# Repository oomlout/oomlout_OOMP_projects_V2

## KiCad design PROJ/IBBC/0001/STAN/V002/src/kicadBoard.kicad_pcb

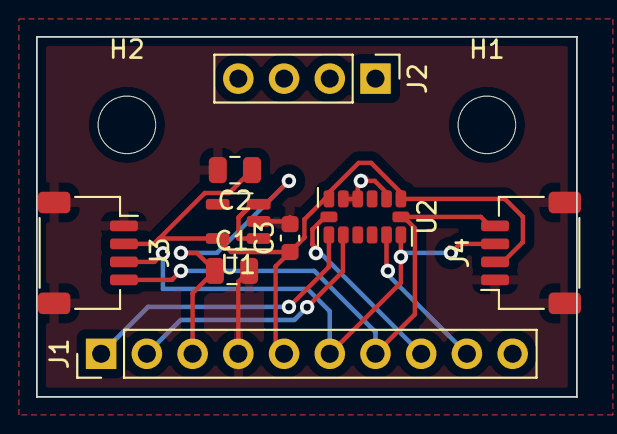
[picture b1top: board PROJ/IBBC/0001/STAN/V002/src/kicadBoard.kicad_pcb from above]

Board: 2 copper layers, 30.0 x 20.0 mm, 11 parts (0 on the bottom side), 9 nets.

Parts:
C1, C2: 10uf; C_0805_2012Metric
C3: 100nf; C_0603_1608Metric
H1, H2: MountingHole; MountingHole_3.2mm_M3
J1: HEAD-I01-X-PI10-01 oom.lt/H10; PinHeader_1x10_P2.54mm_Vertical
J2: HEAD-I01-X-PI04-01 oom.lt/H4; PinHeader_1x04_P2.54mm_Vertical
J3, J4: HEAD-JSTSH-X-PI04-RS oom.lt/HSHR4; JST_SH_SM04B-SRSS-TB_1x04-1MP_P1.00mm_Horizontal
U1: AP2112K-3.3; SOT-23-5
U2: ADXL343; LGA-14_3x5mm_P0.8mm_LayoutBorder1x6y

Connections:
3v3: C2.1, C3.1, J1.5, J3.2, J4.2, U1.5 (VOUT), U2.1 (Vdd_I/O), U2.6 (Vs)
CS: J1.8, U2.7 (~CS)
EX01: J1.1, U2.8 (INT1)
EX02: J1.2, U2.9 (INT2)
EX03: J1.9, U2.12 (SDO/ADDR)
GND: C1.2, C2.2, C3.2, J1.4, J3.1, J3.MP (MountPin), J4.1, J4.MP (MountPin), U1.2 (GND), U2.2 (GND), U2.4 (GND), U2.5 (GND)
SCL: J1.7, J3.4, J4.4, U2.14 (SCL/SCLK)
SDA: J1.6, J3.3, J4.3, U2.13 (SDA/SDI/SDIO)
Vin: C1.1, J1.3, U1.1 (VIN), U1.3 (EN)

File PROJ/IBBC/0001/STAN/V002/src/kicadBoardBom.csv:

"Id";"Designator";"Package";"Quantity";"Designation";"Supplier and ref";
1;"C2,C1";"C_0805_2012Metric";2;"10uf";;;
2;"J1";"PinHeader_1x10_P2.54mm_Vertical";1;"HEAD-I01-X-PI10-01 oom.lt/H10";;;
3;"U1";"SOT-23-5";1;"AP2112K-3.3";;;
4;"J4,J3";"JST_SH_SM04B-SRSS-TB_1x04-1MP_P1.00mm_Horizontal";2;"HEAD-JSTSH-X-PI04-RS oom.lt/HSHR4";;;
5;"U2";"LGA-14_3x5mm_P0.8mm_LayoutBorder1x6y";1;"ADXL343";;;
6;"J2";"PinHeader_1x04_P2.54mm_Vertical";1;"HEAD-I01-X-PI04-01 oom.lt/H4";;;
7;"H2,H1";"MountingHole_3.2mm_M3";2;"MountingHole";;;
8;"C3";"C_0603_1608Metric";1;"100nf";;;

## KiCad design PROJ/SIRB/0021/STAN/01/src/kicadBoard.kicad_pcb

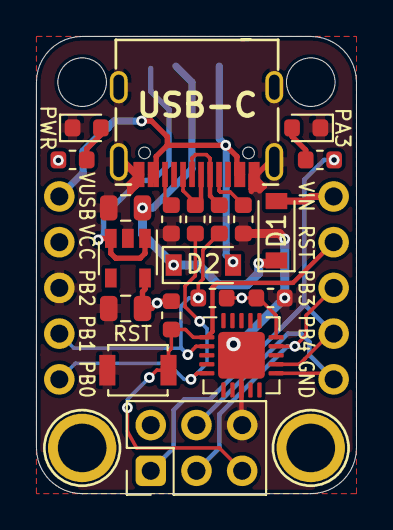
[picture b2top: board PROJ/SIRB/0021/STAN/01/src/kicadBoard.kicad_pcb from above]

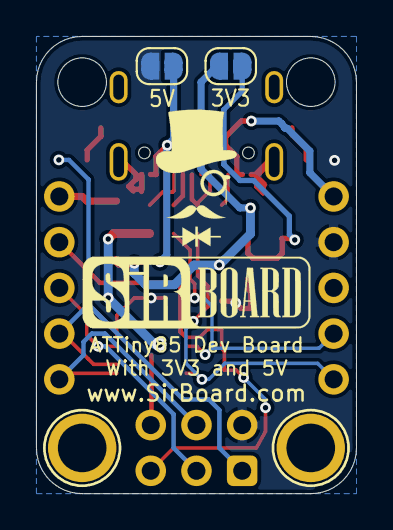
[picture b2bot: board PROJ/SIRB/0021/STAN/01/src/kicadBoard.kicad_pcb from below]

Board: 2 copper layers, 17.8 x 25.4 mm, 28 parts (4 on the bottom side), 18 nets.

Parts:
3V3, 5V: SolderJumper_2_Open; SolderJumper-2_P1.3mm_Open_RoundedPad1.0x1.5mm
C1, C2: 10uF; C_0805_2012Metric
C3: 100nF; C_0603_1608Metric
D1, D2: MBR120; D_SOD-123
H1, H4: MountingHole; MountingHole_2.7mm_M2.5
H2, H3: MountingHole; MountingHole_M2.5_SirBoard
J2, J3: Conn_01x05; PinHeader_1x05_P2.54mm_Vertical
J4: ISP6; PinHeader_2x03_P2.54mm_Vertical
PA3: RED; LED_0603_1608Metric
PWR: RED; LED_0603_1608Metric
R1, R2: 5k1; R_0603_1608Metric
R3, R4: 68e; R_0603_1608Metric
R5: 10K; R_0603_1608Metric
R6: 1k5; R_0603_1608Metric
R7, R8: 1K; R_0603_1608Metric
RST: SW_SPST; SW_SPST_B3U-1000P
U1: ATtiny85-20MU; QFN-20-1EP_4x4mm_P0.5mm_EP2.6x2.6mm
U2: SPX3819M5-L-3-3; SOT-23-5
USB-C: USB_C_Receptacle_USB2.0; USB_C

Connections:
GND: C1.2, C2.2, C3.2, J2.3, J4.6, PA3.1, PWR.1, R1.2, R2.2, RST.2, U1.8, U1.21, U2.2, USB-C.A1, USB-C.A12, USB-C.B1, USB-C.B12, USB-C.S1
unnamed: 3V3.1, C1.1, D1.1, D2.1
unnamed: 3V3.2, U2.1, U2.3
unnamed: PA3.2, R7.1
unnamed: PWR.2, R8.1
unnamed: R2.1, USB-C.A5
unnamed: R4.1, USB-C.A6, USB-C.B6
unnamed: R3.1, USB-C.A7, USB-C.B7
unnamed: R1.1, USB-C.B5
PB0: J3.5, J4.4, U1.11
PB1: J3.4, J4.1, R7.2, U1.12
PB2: J3.3, J4.3, U1.14
PB3: J2.4, R3.2, R6.1, U1.2
PB4: J2.5, R4.2, U1.5
RST: J3.2, J4.5, R5.1, RST.1, U1.1
VCC: 5V.2, C2.1, C3.1, J2.2, J4.2, R5.2, R6.2, R8.2, U1.15, U2.5
VIN: D1.2, J3.1
VUSB: 5V.1, D2.2, J2.1, USB-C.A4, USB-C.A9, USB-C.B4, USB-C.B9

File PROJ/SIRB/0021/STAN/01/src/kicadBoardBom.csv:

"Id";"Designator";"Package";"Quantity";"Designation";"Supplier and ref";
1;"G***";"SirBoard127x40";1;"LOGO";;;
2;"G***";"logo76x107";1;"LOGO";;;
3;"C3";"C_0603_1608Metric";1;"100nF";;;
4;"U1";"QFN-20-1EP_4x4mm_P0.5mm_EP2.6x2.6mm";1;"ATtiny85-20MU";;;
5;"J2,J3";"PinHeader_1x05_P2.54mm_Vertical";2;"Conn_01x05";;;
6;"U2";"SOT-23-5";1;"SPX3819M5-L-3-3";;;
7;"RST";"SW_SPST_B3U-1000P";1;"SW_SPST";;;
8;"R8,R7";"R_0603_1608Metric";2;"1K";;;
9;"R6";"R_0603_1608Metric";1;"1k5";;;
10;"R5";"R_0603_1608Metric";1;"10K";;;
11;"R4,R3";"R_0603_1608Metric";2;"68e";;;
12;"R2,R1";"R_0603_1608Metric";2;"5k1";;;
13;"J4";"PinHeader_2x03_P2.54mm_Vertical";1;"ISP6";;;
14;"USB-C";"USB_C";1;"USB_C_Receptacle_USB2.0";;;
15;"PWR,PA3";"LED_0603_1608Metric";2;"RED";;;
16;"D2,D1";"D_SOD-123";2;"MBR120";;;
17;"C2,C1";"C_0805_2012Metric";2;"10uF";;;

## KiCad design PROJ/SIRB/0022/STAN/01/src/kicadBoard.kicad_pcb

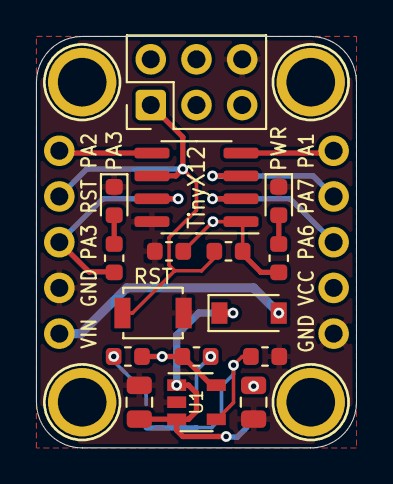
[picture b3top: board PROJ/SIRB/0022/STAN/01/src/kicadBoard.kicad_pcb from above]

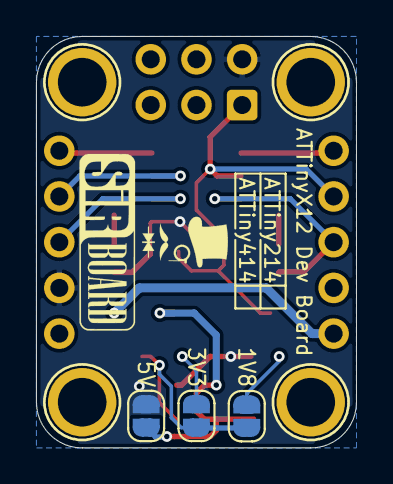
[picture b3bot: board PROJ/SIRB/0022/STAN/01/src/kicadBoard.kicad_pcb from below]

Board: 2 copper layers, 17.8 x 22.9 mm, 25 parts (5 on the bottom side), 15 nets.

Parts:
1V8, 3V3: SolderJumper_2_Open; SolderJumper-2_P1.3mm_Open_RoundedPad1.0x1.5mm
5V: SolderJumper_2_Bridged; SolderJumper-2_P1.3mm_Open_RoundedPad1.0x1.5mm
C1: 10uF; C_0805_2012Metric
C2: 2u2; C_0805_2012Metric
C3: 100nF; C_0603_1608Metric
D1: MBR120; D_SOD-123
H1, H2, H3, H4: MountingHole; MountingHole_M2.5_SirBoard
J1, J2: Conn_01x05; PinHeader_1x05_P2.54mm_Vertical
J4: UPDI; PinHeader_2x03_P2.54mm_Vertical
PA3: BLUE; LED_0603_1608Metric
PWR: RED; LED_0603_1608Metric
R1, R7: 1k; R_0603_1608Metric
R3: 39k; R_0603_1608Metric
R4: 12.4k; R_0603_1608Metric
R5: 18k; R_0603_1608Metric
R6: 10k; R_0603_1608Metric
RST: RST; SW_SPST_B3U-1000P
TinyX12: ATtiny412; SOIC-8_3.9x4.9mm_P1.27mm
U1: AP7365; SOT-23-5

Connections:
/1V8: 1V8.2, R5.2
/3V3: 3V3.2, R3.2
/ADJ: 1V8.1, 3V3.1, R4.1, U1.4
GND: C1.2, C2.2, C3.2, J1.1, J2.2, J4.6, PA3.1, PWR.1, R4.2, RST.2, TinyX12.8, U1.2
unnamed: 5V.1, C1.1, D1.1, U1.1, U1.3
unnamed: PWR.2, R1.2
unnamed: PA3.2, R7.2
PA1: J1.5, TinyX12.4
PA2: J2.5, TinyX12.5
PA3: J2.3, R7.1, TinyX12.7
PA6: J1.3, TinyX12.2
PA7: J1.4, TinyX12.3
RST: J2.4, J4.1, R6.2, RST.1, TinyX12.6
VCC: 5V.2, C2.1, C3.1, J1.2, J4.2, R1.1, R3.1, R5.1, R6.1, TinyX12.1, U1.5
VIN: D1.2, J2.1

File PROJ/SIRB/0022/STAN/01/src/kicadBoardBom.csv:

"Id";"Designator";"Package";"Quantity";"Designation";"Supplier and ref";
1;"G***";"logo47x67";1;"LOGO";;;
2;"D1";"D_SOD-123";1;"MBR120";;;
3;"G***";"SirBoard98x31";1;"LOGO";;;
4;"C3";"C_0603_1608Metric";1;"100nF";;;
5;"C1";"C_0805_2012Metric";1;"10uF";;;
6;"C2";"C_0805_2012Metric";1;"2u2";;;
7;"J2,J1";"PinHeader_1x05_P2.54mm_Vertical";2;"Conn_01x05";;;
8;"TinyX12";"SOIC-8_3.9x4.9mm_P1.27mm";1;"ATtiny412";;;
9;"U1";"SOT-23-5";1;"AP7365";;;
10;"RST";"SW_SPST_B3U-1000P";1;"RST";;;
11;"R7,R1";"R_0603_1608Metric";2;"1k";;;
12;"R6";"R_0603_1608Metric";1;"10k";;;
13;"R5";"R_0603_1608Metric";1;"18k";;;
14;"R4";"R_0603_1608Metric";1;"12.4k";;;
15;"R3";"R_0603_1608Metric";1;"39k";;;
16;"J4";"PinHeader_2x03_P2.54mm_Vertical";1;"UPDI";;;
17;"PA3";"LED_0603_1608Metric";1;"BLUE";;;
18;"PWR";"LED_0603_1608Metric";1;"RED";;;

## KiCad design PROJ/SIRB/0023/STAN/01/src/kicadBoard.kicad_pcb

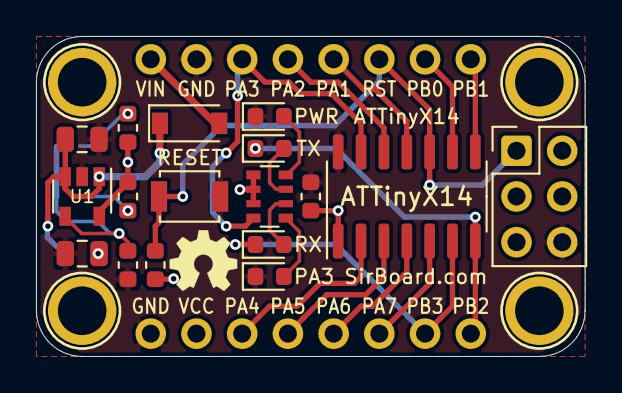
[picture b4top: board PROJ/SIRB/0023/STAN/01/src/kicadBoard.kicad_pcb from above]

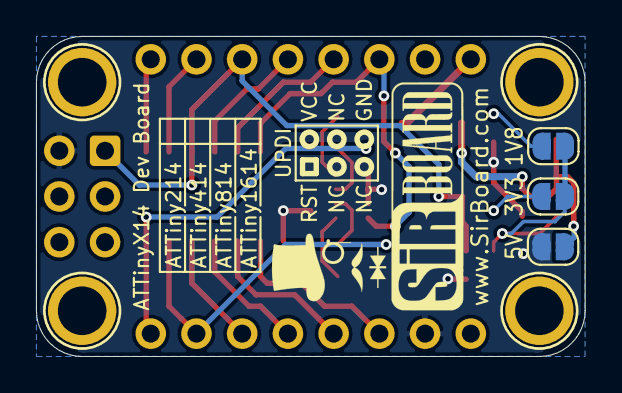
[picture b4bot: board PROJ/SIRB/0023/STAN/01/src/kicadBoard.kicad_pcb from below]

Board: 2 copper layers, 30.5 x 17.8 mm, 26 parts (5 on the bottom side), 23 nets.

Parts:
1V8, 3V3, 5V: SolderJumper_2_Open; SolderJumper-2_P1.3mm_Open_RoundedPad1.0x1.5mm
ATTinyX14: ATtiny1614-SS; SOIC-14_3.9x8.7mm_P1.27mm
C1: 10uF; C_0805_2012Metric
C2: 2u2; C_0805_2012Metric
C3: 100nF; C_0603_1608Metric
D1: MBR120; D_SOD-123
H1, H2, H3, H4: MountingHole; MountingHole_M2.5_SirBoard
J1, J2: Conn_01x08; PinHeader_1x08_P2.54mm_Vertical
J4: UPDI; PinHeader_2x03_P2.54mm_Vertical
PA3: BLUE; LED_0603_1608Metric
PWR: RED; LED_0603_1608Metric
R3: 39k; R_0603_1608Metric
R4: 12.4k; R_0603_1608Metric
R5: 18k; R_0603_1608Metric
R6: 10k; R_0603_1608Metric
RESET: RST; SW_SPST_B3U-1000P
RN1: 330E; R_Array_Convex_4x0603
RX: YEL; LED_0603_1608Metric
TX: YEL; LED_0603_1608Metric
U1: AP7365; SOT-23-5

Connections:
/1V8: 1V8.2, R5.2
/3V3: 3V3.2, R3.2
/ADJ: 1V8.1, 3V3.1, R4.1, U1.4
GND: ATTinyX14.14, C1.2, C2.2, C3.2, J1.1, J2.2, J4.6, PA3.1, PWR.1, R4.2, RESET.2, U1.2
unnamed: 5V.2, C1.1, D1.1, U1.1, U1.3
unnamed: PA3.2, RN1.1
unnamed: PWR.2, RN1.4
unnamed: RN1.2, RX.2
unnamed: RN1.3, TX.2
PA1: ATTinyX14.11, J2.5
PA2: ATTinyX14.12, J2.4
PA3: ATTinyX14.13, J2.3, RN1.8
PA4: ATTinyX14.2, J1.3
PA5: ATTinyX14.3, J1.4
PA6: ATTinyX14.4, J1.5
PA7: ATTinyX14.5, J1.6
PB0: ATTinyX14.9, J2.7
PB1: ATTinyX14.8, J2.8
RST: ATTinyX14.10, J2.6, J4.1, R6.2, RESET.1
RXD: ATTinyX14.6, J1.7, RX.1
TXD: ATTinyX14.7, J1.8, TX.1
VCC: 5V.1, ATTinyX14.1, C2.1, C3.1, J1.2, J4.2, R3.1, R5.1, R6.1, RN1.5, RN1.6, RN1.7, U1.5
VIN: D1.2, J2.1

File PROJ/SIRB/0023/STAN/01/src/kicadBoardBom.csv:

"Id";"Designator";"Package";"Quantity";"Designation";"Supplier and ref";
1;"G***";"SirBoard127x40";1;"LOGO";;;
2;"G***";"logo63x89";1;"LOGO";;;
3;"G***";"OSHW55x39";1;"LOGO";;;
4;"RN1";"R_Array_Convex_4x0603";1;"330E";;;
5;"TX,RX";"LED_0603_1608Metric";2;"YEL";;;
6;"ATTinyX14";"SOIC-14_3.9x8.7mm_P1.27mm";1;"ATtiny1614-SS";;;
7;"J2,J1";"PinHeader_1x08_P2.54mm_Vertical";2;"Conn_01x08";;;
8;"D1";"D_SOD-123";1;"MBR120";;;
9;"C3";"C_0603_1608Metric";1;"100nF";;;
10;"C1";"C_0805_2012Metric";1;"10uF";;;
11;"C2";"C_0805_2012Metric";1;"2u2";;;
12;"U1";"SOT-23-5";1;"AP7365";;;
13;"RESET";"SW_SPST_B3U-1000P";1;"RST";;;
14;"R6";"R_0603_1608Metric";1;"10k";;;
15;"R5";"R_0603_1608Metric";1;"18k";;;
16;"R4";"R_0603_1608Metric";1;"12.4k";;;
17;"R3";"R_0603_1608Metric";1;"39k";;;
18;"J4";"PinHeader_2x03_P2.54mm_Vertical";1;"UPDI";;;
19;"PA3";"LED_0603_1608Metric";1;"BLUE";;;
20;"PWR";"LED_0603_1608Metric";1;"RED";;;

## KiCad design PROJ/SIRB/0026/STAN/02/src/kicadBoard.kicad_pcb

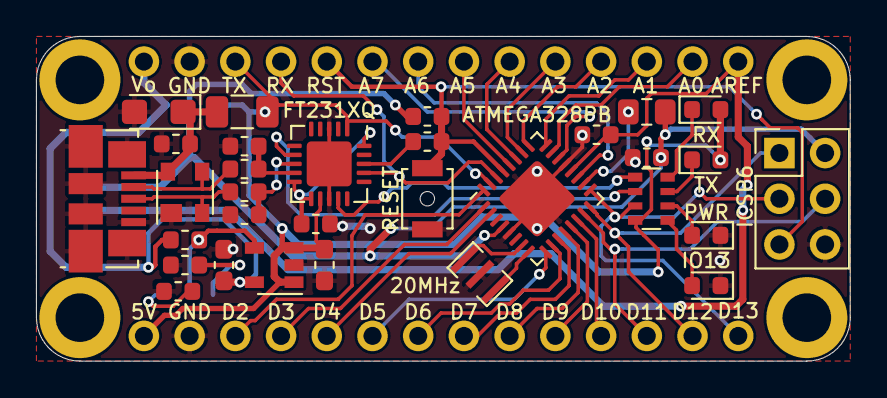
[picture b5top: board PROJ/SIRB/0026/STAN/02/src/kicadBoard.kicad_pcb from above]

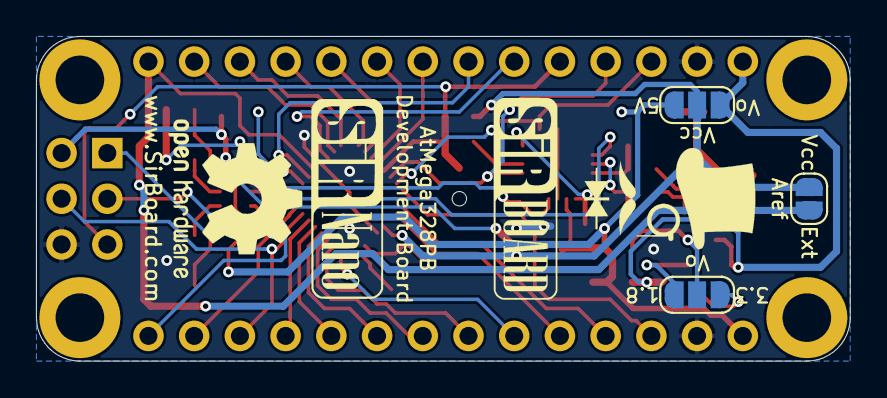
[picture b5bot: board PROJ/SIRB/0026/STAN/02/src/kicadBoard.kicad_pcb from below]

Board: 2 copper layers, 45.2 x 18.0 mm, 36 parts (5 on the bottom side), 47 nets.

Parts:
20MHz: 20MHz; Resonator_SMD_muRata_CSTxExxV-3Pin_3.0x1.1mm
C1, C3, C11: 100nF; C_0603_1608Metric
C2, C4: 47pF; C_0603_1608Metric
C6: 10nF; C_0603_1608Metric
C7: 1uF; C_0603_1608Metric
C8: 22uF; CP_EIA-3216-12_Kemet-S
C9, C10: 1uF; C_0603_1608Metric_Pad1.05x0.95mm_HandSolder
D1: PRTR5V0U2X; SOT-143
F1: 500mA; R_1206_3216Metric
FT231XQ: FT231XQ; QFN-20-1EP_4x4mm_P0.5mm_EP2.5x2.5mm
ICSP6: Conn_02x03_Odd_Even; PinHeader_2x03_P2.54mm_Vertical
IO13: LED; LED_0603_1608Metric
J1, J2: Conn_01x14; PinHeader_1x14_P2.54mm_Vertical
J3: USB_B_Micro; USB_Micro-B_Molex_47346-0001
JP1: SolderJumper_2_Bridged; SolderJumper-2_P1.3mm_Open_RoundedPad1.0x1.5mm
JP2, JP3: SolderJumper_3_Open; SolderJumper-3_P1.3mm_Open_RoundedPad1.0x1.5mm
L1: 10uH; L_0805_2012Metric_Pad1.15x1.40mm_HandSolder
PWR: LED; LED_0603_1608Metric
R1, R2: 27e; R_0603_1608Metric
R3: 10k; R_0603_1608Metric
R5: 56k; R_0603_1608Metric
R6: 22k; R_0603_1608Metric
R7: 68k; R_0603_1608Metric
RESET: SW_Push; SW_SPST_B3U-1000P-B
RN1: R_Pack04; R_Array_Convex_4x0603
RX: LED; LED_0603_1608Metric
TX: LED; LED_0603_1608Metric
U1: ATmega328PB-MU; QFN-32-1EP_5x5mm_P0.5mm_EP3.1x3.1mm
U2: AP7365-ADJ; SOT-23-5

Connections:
1.8V: JP2.3, R5.1
3.3V: C3.1, FT231XQ.10, FT231XQ.11, FT231XQ.20
3_3V: JP2.1, R6.1
5V: C9.1, F1.1, FT231XQ.12, J1.1, JP3.3, RN1.4, RX.2, TX.2, U2.1, U2.3
/IO13LED: IO13.2, RN1.5
/PWRLED: PWR.2, RN1.6
/X1: 20MHz.3, U1.7
/X2: 20MHz.1, U1.8
/uD+: C2.1, FT231XQ.8, R2.2
/uD-: C4.1, FT231XQ.9, R1.2
A0: J2.13, U1.23
A1: J2.12, U1.24
A2: J2.11, U1.25
A3: J2.10, U1.26
A4: J2.9, U1.27
A5: J2.8, U1.28
A6: J2.7, U1.19
A7: J2.6, U1.22
ADJ: JP2.2, R7.2, U2.4
AREF: C1.1, J2.14, JP1.1, U1.20
D2: J1.3, U1.32
D3: J1.4, U1.1
D4: J1.5, U1.2
D5: J1.6, U1.9
D6: J1.7, U1.10
D7: J1.8, U1.11
D8: J1.9, U1.12
D9: J1.10, U1.13
D10: J1.11, U1.14
D11: ICSP6.4, J1.12, U1.15
D12: ICSP6.1, J1.13, U1.16
D13: ICSP6.3, J1.14, RN1.3, U1.17
D+: D1.2, J3.3, R2.1
D-: D1.3, J3.2, R1.1
GND: 20MHz.2, C1.2, C2.2, C3.2, C4.2, C6.2, C7.2, C8.2, C9.2, C10.2, D1.1, FT231XQ.3, FT231XQ.13, FT231XQ.21, ICSP6.6, IO13.1, J1.2, J2.2, J3.5, J3.6, PWR.1, R5.2, R6.2, RESET.2, U1.5, U1.21, U1.33, U2.2
unnamed: C11.2, FT231XQ.18
unnamed: L1.2, U1.18
unnamed: RN1.7, TX.1
unnamed: RN1.8, RX.1
RESET: C11.1, ICSP6.5, J2.5, R3.2, RESET.1, U1.29
RX: FT231XQ.17, J2.4, U1.30
RX_LED: FT231XQ.14, RN1.1
TX: FT231XQ.1, J2.3, U1.31
TX_LED: FT231XQ.7, RN1.2
VBUS: C6.1, C8.1, D1.4, F1.2, J3.1
VCC: C7.1, ICSP6.2, JP1.2, JP3.2, L1.1, R3.1, U1.4
VOUT: C10.1, J2.1, JP3.1, R7.1, U2.5

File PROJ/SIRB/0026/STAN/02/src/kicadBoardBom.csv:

"Id";"Designator";"Package";"Quantity";"Designation";"Supplier and ref";
1;"RN1";"R_Array_Convex_4x0603";1;"R_Pack04";;;
2;"R5";"R_0603_1608Metric";1;"56k";;;
3;"C11,C3,C1";"C_0603_1608Metric";3;"100nF";;;
4;"C10,C9";"C_0603_1608Metric_Pad1.05x0.95mm_HandSolder";2;"1uF";;;
5;"F1";"R_1206_3216Metric";1;"500mA";;;
6;"G***";"logo94x134";1;"LOGO";;;
7;"RESET";"SW_SPST_B3U-1000P-B";1;"SW_Push";;;
8;"C7";"C_0603_1608Metric";1;"1uF";;;
9;"R7";"R_0603_1608Metric";1;"68k";;;
10;"D1";"SOT-143";1;"PRTR5V0U2X";;;
11;"R3";"R_0603_1608Metric";1;"10k";;;
12;"R6";"R_0603_1608Metric";1;"22k";;;
13;"J1,J2";"PinHeader_1x14_P2.54mm_Vertical";2;"Conn_01x14";;;
14;"G***";"SirNano118x40";1;"LOGO";;;
15;"G***";"SirBoard112x35";1;"LOGO";;;
16;"U2";"SOT-23-5";1;"AP7365-ADJ";;;
17;"20MHz";"Resonator_SMD_muRata_CSTxExxV-3Pin_3.0x1.1mm";1;"20MHz";;;
18;"U1";"QFN-32-1EP_5x5mm_P0.5mm_EP3.1x3.1mm";1;"ATmega328PB-MU";;;
19;"TX,RX,PWR,IO13";"LED_0603_1608Metric";4;"LED";;;
20;"R2,R1";"R_0603_1608Metric";2;"27e";;;
21;"L1";"L_0805_2012Metric_Pad1.15x1.40mm_HandSolder";1;"10uH";;;
22;"C8";"CP_EIA-3216-12_Kemet-S";1;"22uF";;;
23;"C6";"C_0603_1608Metric";1;"10nF";;;
24;"C4,C2";"C_0603_1608Metric";2;"47pF";;;
25;"ICSP6";"PinHeader_2x03_P2.54mm_Vertical";1;"Conn_02x03_Odd_Even";;;
26;"FT231XQ";"QFN-20-1EP_4x4mm_P0.5mm_EP2.5x2.5mm";1;"FT231XQ";;;
27;"J3";"USB_Micro-B_Molex_47346-0001";1;"USB_B_Micro";;;

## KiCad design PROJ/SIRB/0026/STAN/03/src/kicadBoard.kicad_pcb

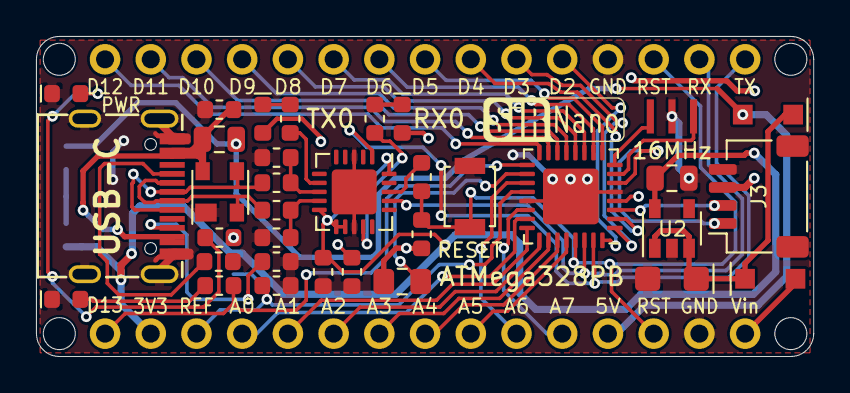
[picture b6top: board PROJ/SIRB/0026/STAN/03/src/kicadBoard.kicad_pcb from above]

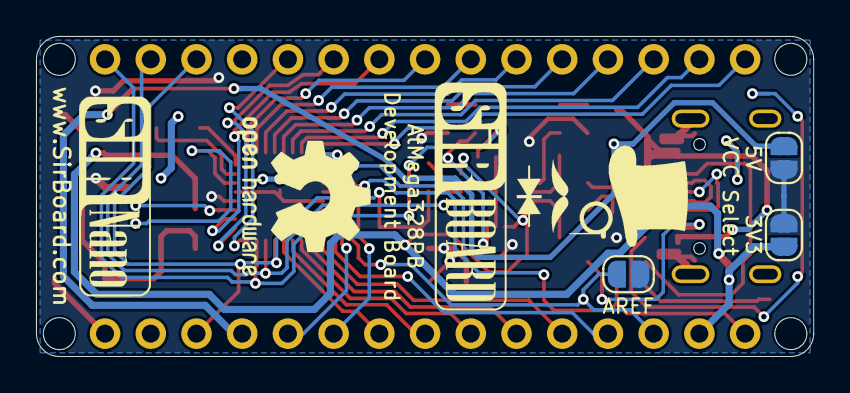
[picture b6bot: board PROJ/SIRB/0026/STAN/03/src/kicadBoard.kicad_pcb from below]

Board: 2 copper layers, 43.2 x 17.8 mm, 43 parts (5 on the bottom side), 49 nets.

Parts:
C1, C3, C9, C11: 100nF; C_0603_1608Metric
C2, C4: 47pF; C_0603_1608Metric
C6: 10nF; C_0603_1608Metric
C7: 10uF; C_0805_2012Metric
C8: 22uF; CP_EIA-3216-12_Kemet-S
D1: PRTR5V0U2X; SOT-143
D2, D3: MBR120; D_SOD-123F
D13: LED; LED_0603_1608Metric
F1: 500mA; R_0805_2012Metric
H1, H2, H3, H4: MountingHole; MountingHole_2.2mm_M2
J1, J2: Conn_01x15; PinHeader_1x15_P2.54mm_Vertical
J3: SirBlue; SirBlue_Connector
JP1, JP2, JP3: AREF; SolderJumper-2_P1.3mm_Open_RoundedPad1.0x1.5mm
L1: 10uH; L_0805_2012Metric_Pad1.15x1.40mm_HandSolder
PWR: LED; LED_0603_1608Metric
R1, R2: 27e; R_0603_1608Metric
R3: 10k; R_0603_1608Metric
R4, R8, R9, R10: 1k; R_0603_1608Metric
R11, R12: 5K1; R_0603_1608Metric
RESET: SW_Push; SW_SPST_B3U-1000P
RX0: LED; LED_0603_1608Metric
TX0: LED; LED_0603_1608Metric
U1: ATmega328PB-MU; QFN-32-1EP_5x5mm_P0.5mm_EP3.1x3.1mm
U2: SPX3819M5-L-3-3; SOT-23-5
U3: FT231XQ; QFN-20-1EP_4x4mm_P0.5mm_EP2.5x2.5mm
USB-C: USB_C_Plug_USB2.0; USB_C
Y1: 16MHz; Resonator_SMD_muRata_CSTxExxV-3Pin_3.0x1.1mm

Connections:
3V3: C3.1, C7.1, J2.14, JP3.1, U2.5, U3.10, U3.11, U3.12, U3.20
/D13LED: D13.2, R9.2
/LDO_in: C8.1, D2.1, D3.1, U2.1, U2.3
/PWRLED: PWR.2, R10.2
/RXLED: R4.2, RX0.1
/TXLED: R8.2, TX0.1
/X1: U1.7, Y1.3
/X2: U1.8, Y1.1
/uD+: C2.1, R1.2, U3.8
/uD-: C4.1, R2.2, U3.9
A0: J2.12, U1.23
A1: J2.11, U1.24
A2: J2.10, U1.25
A3: J2.9, U1.26
A4: J2.8, U1.27
A5: J2.7, U1.28
A6: J2.6, U1.19
A7: J2.5, U1.22
AREF: C1.1, J2.13, JP1.1, U1.20
D2: J1.11, U1.32
D3: J1.10, U1.1
D4: J1.9, U1.2
D5: J1.8, U1.9
D6: J1.7, U1.10
D7: J1.6, U1.11
D8: J1.5, U1.12
D9: J1.4, U1.13
D10: J1.3, U1.14
D11: J1.2, U1.15
D12: J1.1, U1.16
D13: J2.15, R9.1, U1.17
D+: D1.3, R1.1, USB-C.A6, USB-C.B6
D-: D1.2, R2.1, USB-C.A7, USB-C.B7
GND: C1.2, C2.2, C3.2, C4.2, C6.2, C7.2, C8.2, C9.2, D1.1, D13.1, J1.12, J2.2, J3.4, PWR.1, R11.1, R12.1, RESET.2, U1.5, U1.21, U1.33, U2.2, U3.3, U3.13, U3.21, USB-C.A1, USB-C.A12, USB-C.B1, USB-C.B12, USB-C.S1, Y1.2
unnamed: C11.2, U3.18
unnamed: L1.2, U1.18
unnamed: R12.2, USB-C.A5
unnamed: R11.2, USB-C.B5
RESET: C11.1, J1.13, J2.3, R3.2, RESET.1, U1.29
RX: J1.14, U1.30, U3.17
RX_LED: R4.1, U3.14
SCL1: J3.1, U1.6
SDA1: J3.2, U1.3
TX: J1.15, U1.31, U3.1
TX_LED: R8.1, U3.7
VBUS: C6.1, D1.4, F1.2, USB-C.A4, USB-C.A9, USB-C.B4, USB-C.B9
VCC: C9.1, J3.3, JP1.2, JP2.2, JP3.2, L1.1, R3.1, R10.1, RX0.2, TX0.2, U1.4
VIN: D3.2, J2.1
VUSB: D2.2, F1.1, J2.4, JP2.1

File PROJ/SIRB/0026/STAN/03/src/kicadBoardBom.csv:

"Id";"Designator";"Package";"Quantity";"Designation";"Supplier and ref";
1;"G***";"SirBoard79x25";1;"LOGO";;;
2;"USB-C";"USB_C";1;"USB_C_Plug_USB2.0";;;
3;"G***";"SirBoard127x40";1;"LOGO";;;
4;"D2,D3";"D_SOD-123F";2;"MBR120";;;
5;"C8";"CP_EIA-3216-12_Kemet-S";1;"22uF";;;
6;"Y1";"Resonator_SMD_muRata_CSTxExxV-3Pin_3.0x1.1mm";1;"16MHz";;;
7;"U2";"SOT-23-5";1;"SPX3819M5-L-3-3";;;
8;"U1";"QFN-32-1EP_5x5mm_P0.5mm_EP3.1x3.1mm";1;"ATmega328PB-MU";;;
9;"G***";"SirNano118x40";1;"LOGO";;;
10;"G***";"logo94x134";1;"LOGO";;;
11;"R12,R11";"R_0603_1608Metric";2;"5K1";;;
12;"J3";"SirBlue_Connector";1;"SirBlue";;;
13;"RESET";"SW_SPST_B3U-1000P";1;"SW_Push";;;
14;"D1";"SOT-143";1;"PRTR5V0U2X";;;
15;"F1";"R_0805_2012Metric";1;"500mA";;;
16;"PWR,D13,TX0,RX0";"LED_0603_1608Metric";4;"LED";;;
17;"R10,R9,R8,R4";"R_0603_1608Metric";4;"1k";;;
18;"R3";"R_0603_1608Metric";1;"10k";;;
19;"L1";"L_0805_2012Metric_Pad1.15x1.40mm_HandSolder";1;"10uH";;;
20;"C11,C9,C3,C1";"C_0603_1608Metric";4;"100nF";;;
21;"C7";"C_0805_2012Metric";1;"10uF";;;
22;"J1,J2";"PinHeader_1x15_P2.54mm_Vertical";2;"Conn_01x15";;;
23;"U3";"QFN-20-1EP_4x4mm_P0.5mm_EP2.5x2.5mm";1;"FT231XQ";;;
24;"R2,R1";"R_0603_1608Metric";2;"27e";;;
25;"C6";"C_0603_1608Metric";1;"10nF";;;
26;"C4,C2";"C_0603_1608Metric";2;"47pF";;;
